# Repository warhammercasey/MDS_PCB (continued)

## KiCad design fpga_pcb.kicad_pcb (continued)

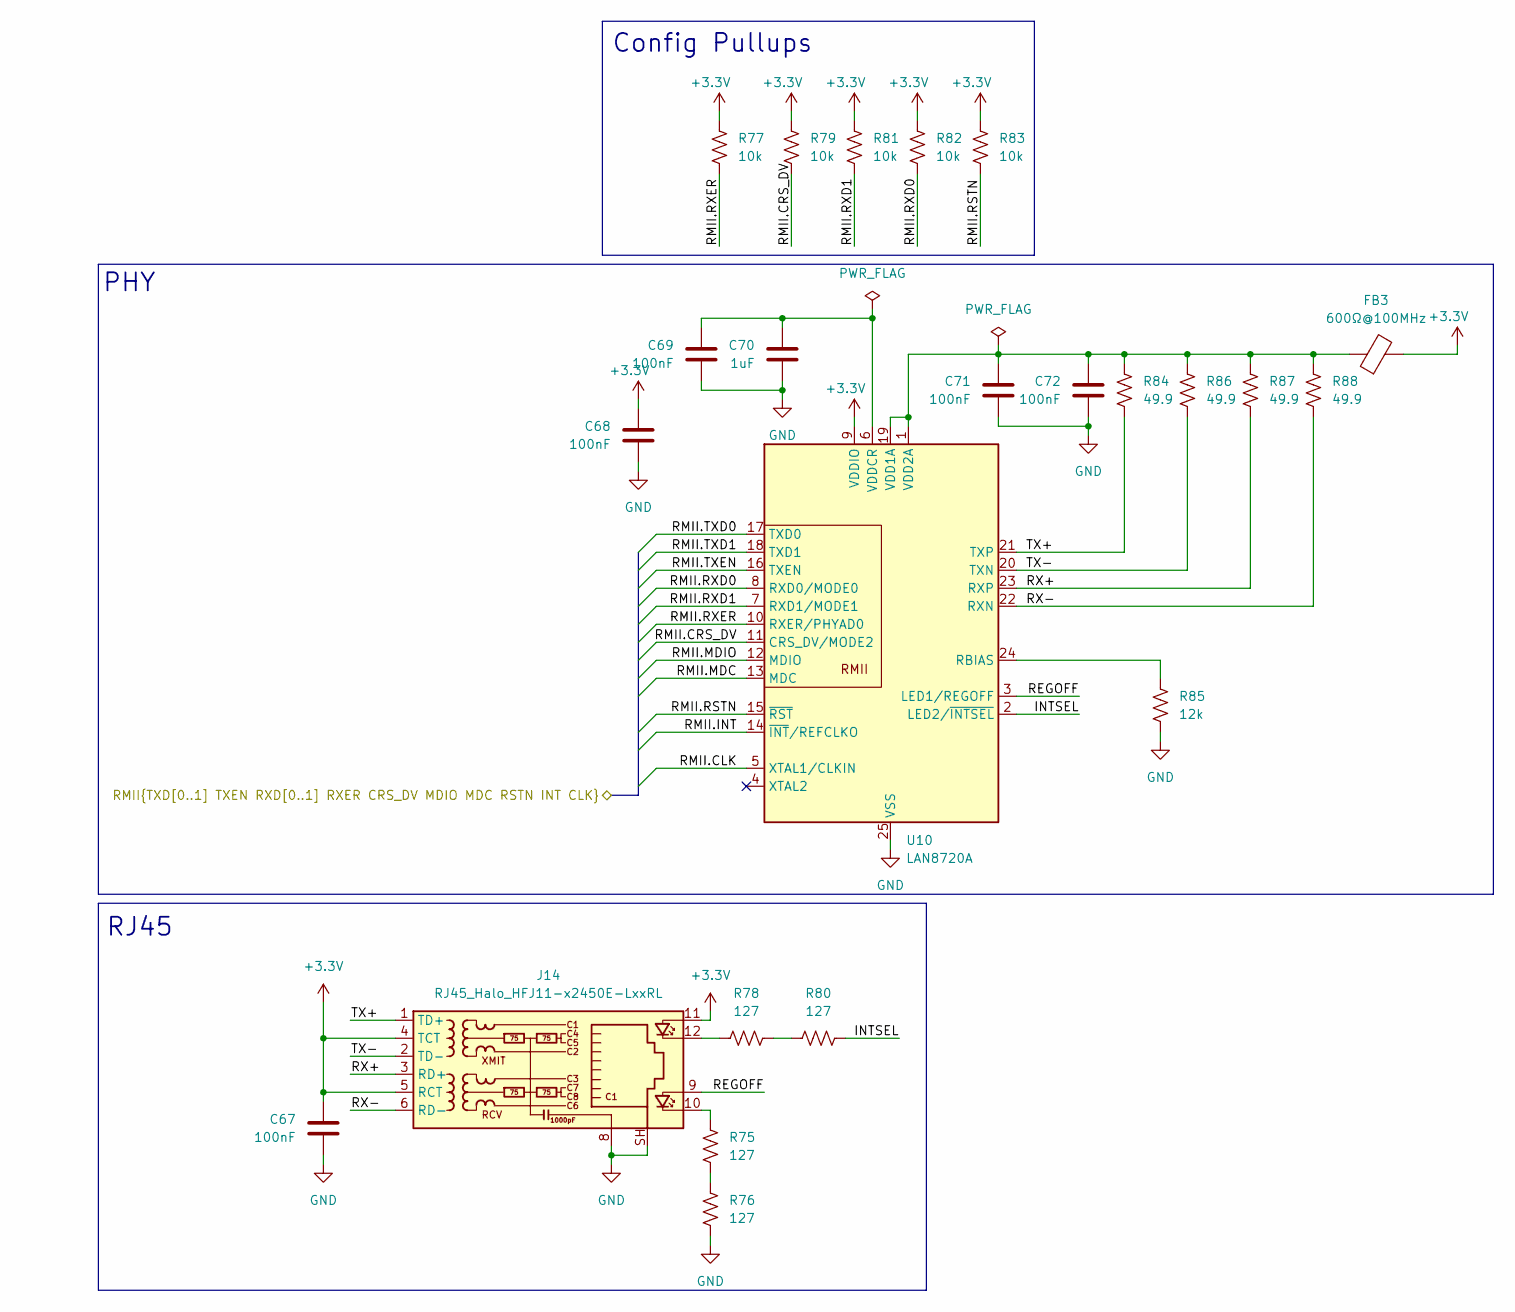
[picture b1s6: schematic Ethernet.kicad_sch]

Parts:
C67, C68, C69, C71, C72: 100nF; C_0603_1608Metric; Digikey PN 1276-6854-1-ND
C70: 1uF; C_0603_1608Metric; Digikey PN 1276-1859-1-ND
FB3: 600Ω@100MHz; L_0603_1608Metric; Digikey PN 490-1014-1-ND
J14: RJ45_Halo_HFJ11-x2450E-LxxRL; RJ45_HALO_HFJ11-x2450E-LxxRL_Horizontal; Digikey PN 5843-HFJ11-2450E-L12RL-ND
R75, R76, R78, R80: 127; R_0603_1608Metric; Digikey PN 311-127HRCT-ND
R77, R79, R81, R82, R83: 10k; R_0603_1608Metric; Digikey PN 311-10KLDCT-ND
R84, R86, R87, R88: 49.9; R_0603_1608Metric; Digikey PN 311-49.9HRCT-ND
R85: 12k; R_0603_1608Metric; Digikey PN 311-12.0KHRCT-ND
U10: LAN8720A; VQFN-24-1EP_4x4mm_P0.5mm_EP2.5x2.5mm_ThermalVias; Digikey PN LAN8720A-CP-CT-ND

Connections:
+3.3V: C67.1, C68.1, FB3.2, J14.4 (TCT), J14.5 (RCT), J14.11, R77.1, R79.1, R81.1, R82.1, R83.1, U10.9 (VDDIO); also elsewhere on the board
/Ethernet/INTSEL: R80.1, U10.2 (LED2/~INTSEL)
/Ethernet/REGOFF: J14.9, U10.3 (LED1/REGOFF)
/Ethernet/RMII.CLK: U10.5 (XTAL1/CLKIN); also elsewhere on the board
/Ethernet/RMII.CRS_DV: R79.2, U10.11 (CRS_DV/MODE2); also elsewhere on the board
/Ethernet/RMII.INT: U10.14 (~INT/REFCLKO); also elsewhere on the board
/Ethernet/RMII.MDC: U10.13 (MDC); also elsewhere on the board
/Ethernet/RMII.MDIO: U10.12 (MDIO); also elsewhere on the board
/Ethernet/RMII.RSTN: R83.2, U10.15 (~RST); also elsewhere on the board
/Ethernet/RMII.RXD0: R82.2, U10.8 (RXD0/MODE0); also elsewhere on the board
/Ethernet/RMII.RXD1: R81.2, U10.7 (RXD1/MODE1); also elsewhere on the board
/Ethernet/RMII.RXER: R77.2, U10.10 (RXER/PHYAD0); also elsewhere on the board
/Ethernet/RMII.TXD0: U10.17 (TXD0); also elsewhere on the board
/Ethernet/RMII.TXD1: U10.18 (TXD1); also elsewhere on the board
/Ethernet/RMII.TXEN: U10.16 (TXEN); also elsewhere on the board
/Ethernet/RX+: J14.3 (RD+), R87.2, U10.23 (RXP)
/Ethernet/RX-: J14.6 (RD-), R88.2, U10.22 (RXN)
/Ethernet/TX+: J14.1 (TD+), R84.2, U10.21 (TXP)
/Ethernet/TX-: J14.2 (TD-), R86.2, U10.20 (TXN)
GND: C67.2, C68.2, C69.2, C70.2, C71.2, C72.2, J14.8, J14.SH, R76.2, R85.2, U10.25 (VSS); also elsewhere on the board
unnamed: J14.10, R75.1
unnamed: J14.12, R78.2
unnamed: R75.2, R76.1
unnamed: R78.1, R80.2
unnamed: R85.1, U10.24 (RBIAS)
unnamed: C71.1, C72.1, FB3.1, R84.1, R86.1, R87.1, R88.1, U10.1 (VDD2A), U10.19 (VDD1A)
unnamed: C69.1, C70.1, U10.6 (VDDCR)

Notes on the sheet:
RJ45
Config Pullups
PHY

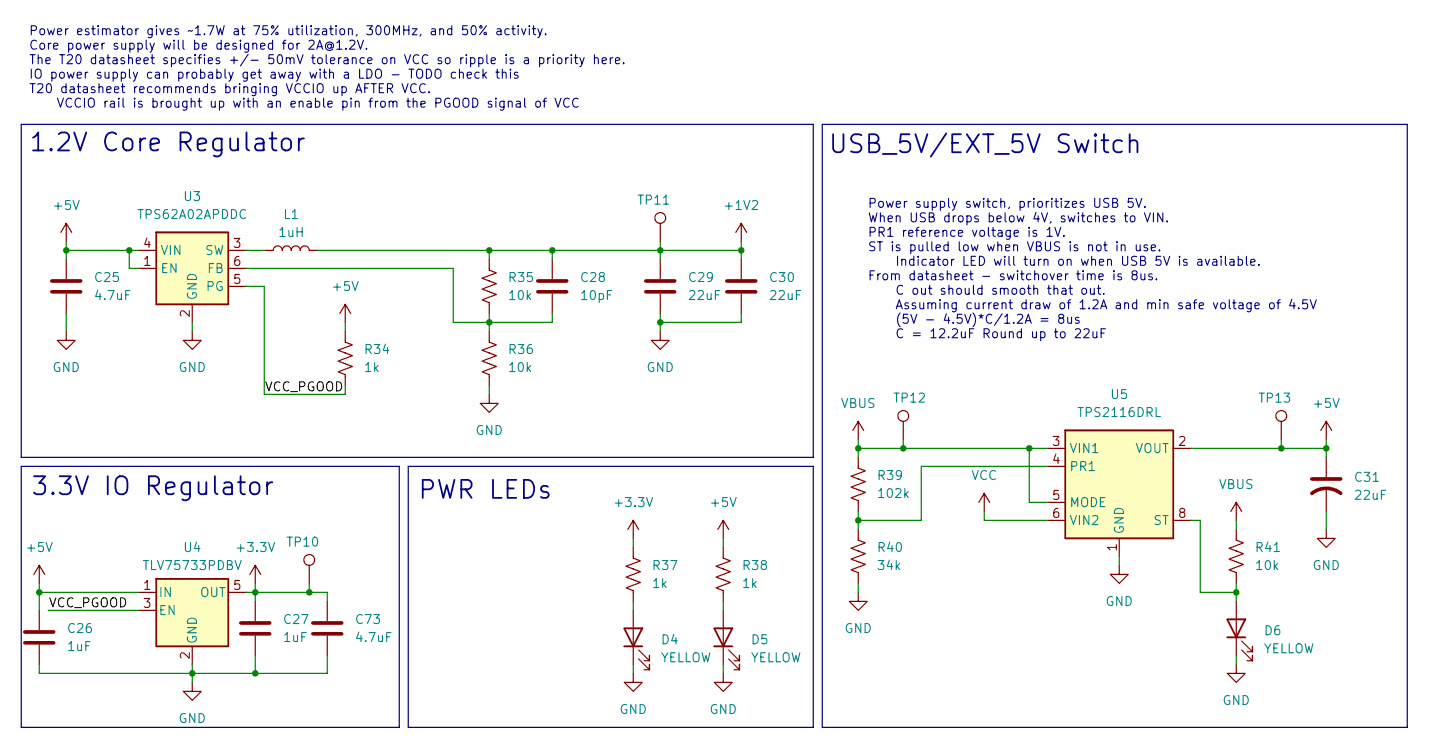
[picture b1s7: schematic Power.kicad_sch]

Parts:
C25, C73: 4.7uF; C_0603_1608Metric; Digikey PN 1276-1045-1-ND
C26, C27: 1uF; C_0603_1608Metric; Digikey PN 1276-1859-1-ND
C28: 10pF; C_0603_1608Metric; Digikey PN 1276-2149-1-ND
C29, C30: 22uF; C_1206_3216Metric; Digikey PN 1276-2728-1-ND
C31: 22uF; C_Radial_D5.0mm_H7.0mm_P2.00mm; Digikey PN P814-ND
D4, D5, D6: YELLOW; LED_0603_1608Metric; Digikey PN 754-1124-1-ND
L1: 1uH; L_1210_3225Metric; Digikey PN 3526-WIP322512A-1R0MLDGCT-ND
R34, R37, R38: 1k; R_0603_1608Metric; Digikey PN 311-1.00KHRCT-ND
R35, R36, R41: 10k; R_0603_1608Metric; Digikey PN 311-10KLDCT-ND
R39: 102k; R_0603_1608Metric; Digikey PN YAG1498CT-ND
R40: 34k; R_0603_1608Metric; Digikey PN 311-34.0KHRCT-ND
TP10, TP11, TP12, TP13: TestPoint; TestPoint_Pad_D1.0mm
U3: TPS62A02APDDC; SOT-23-6; Digikey PN 296-TPS62A02APDDCRCT-ND
U4: TLV75733PDBV; SOT-23-5; Digikey PN 296-TLV75733PDYDRCT-ND
U5: TPS2116DRL; SOT-583-8; Digikey PN 296-TPS2116DRLRCT-ND

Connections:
+1V2: C28.1, C29.1, C30.1, L1.2, R35.1, TP11.1 (1_1); also elsewhere on the board
+3.3V: C27.1, C73.1, R37.1, TP10.1 (1_1), U4.5 (OUT); also elsewhere on the board
+5V: C25.1, C26.1, C31.1, R34.1, R38.1, TP13.1 (1_1), U3.1 (EN), U3.4 (VIN), U4.1 (IN), U5.2 (VOUT), U5.7 (VOUT)
/Power/VCC_PGOOD: R34.2, U3.5 (PG), U4.3 (EN)
GND: C25.2, C26.2, C27.2, C29.2, C30.2, C31.2, C73.2, D4.1 (K), D5.1 (K), D6.1 (K), R36.2, R40.2, U3.2 (GND), U4.2 (GND), U5.1 (GND); also elsewhere on the board
unnamed: D4.2 (A), R37.2
unnamed: D5.2 (A), R38.2
unnamed: D6.2 (A), R41.2, U5.8 (ST)
unnamed: C28.2, R35.2, R36.1, U3.6 (FB)
unnamed: L1.1, U3.3 (SW)
unnamed: R39.2, R40.1, U5.4 (PR1)
VBUS: R39.1, R41.1, TP12.1 (1_1), U5.3 (VIN1), U5.5 (MODE); also elsewhere on the board
VCC: U5.6 (VIN2); also elsewhere on the board

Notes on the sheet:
USB_5V/EXT_5V Switch
PWR LEDs
Power estimator gives ~1.7W at 75% utilization, 300MHz, and 50% activity. Core power supply will be designed for 2A@1.2V. The T20 datasheet specifies +/- 50mV tolerance on VCC so ripple is a priority here. IO power supply can probably get away with a LDO - TODO check this T20 datasheet recommends b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
1.2V Core Regulator
Power supply switch, prioritizes USB 5V. When USB drops below 4V, switches to VIN. PR1 reference voltage is 1V. ST is pulled low when VBUS is not in use. Indicator LED will turn on when USB 5V is available. From datasheet - switchover time is 8us. C out should smooth that out. Assuming current draw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
3.3V IO Regulator

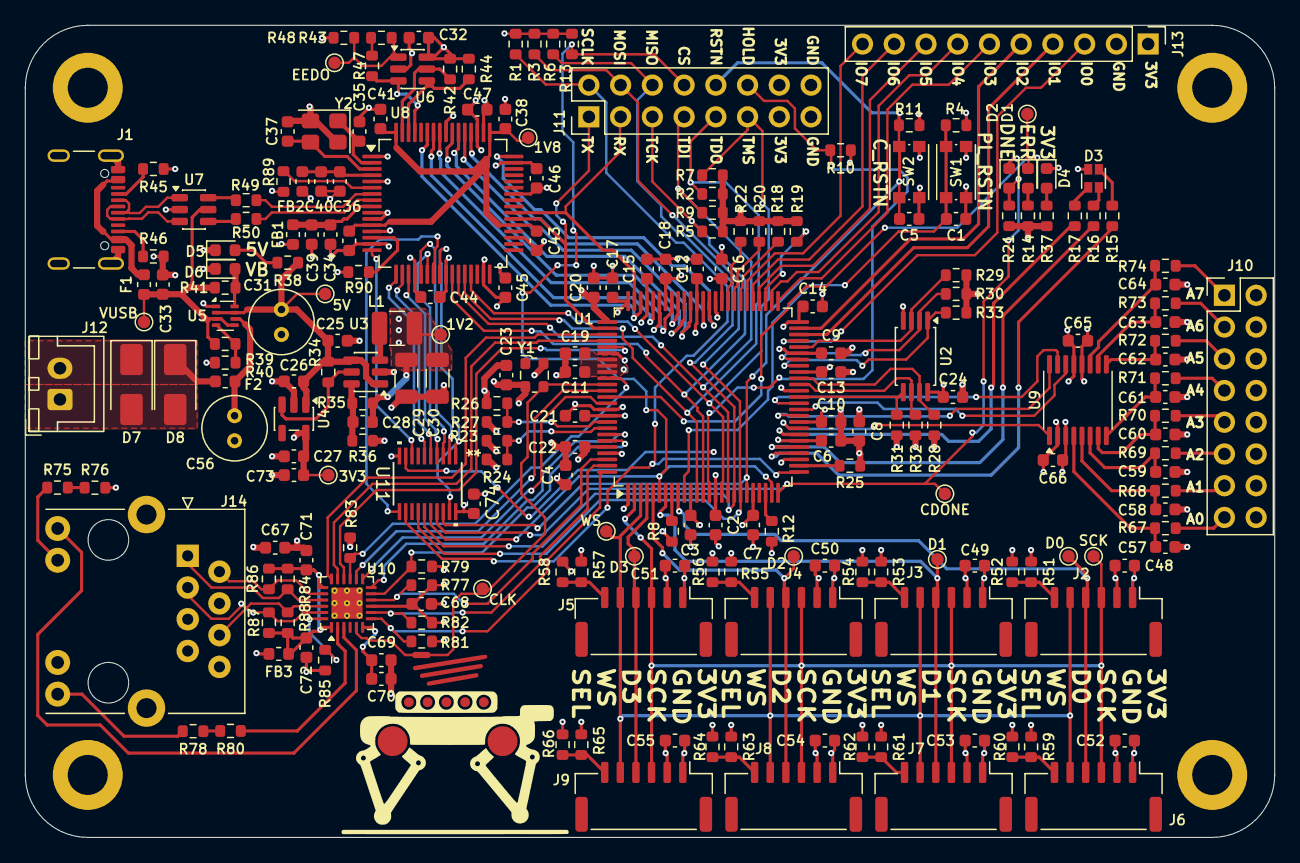
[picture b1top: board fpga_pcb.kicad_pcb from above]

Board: 4 copper layers, 100.0 x 65.0 mm, 227 parts (0 on the bottom side), 156 nets.

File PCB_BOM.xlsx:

Reference | Qty | Value | DNP | Exclude from BOM | Exclude from Board | Digikey PN | Unit Cost | Description | Total Cost | Board cost:
C1,C2,C3,C5,C6,C7,C9,C10,C12,C13,C15,C16,C17,C18,C19,C20,C21,C22,C23,C24,C32,C3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 | 46 | 100nF |  |  |  | 1276-6854-1-ND | 5.5E-2 | Unpolarized capacitor | 2.5299999999999998 | 56.957000000000001
C4,C8,C11,C14,C25,C34,C36,C38,C48,C49,C50,C51,C52,C53,C54,C55,C73 | 17 | 4.7uF |  |  |  | 1276-1045-1-ND | 4.3999999999999997E-2 | Unpolarized capacitor | 0.748
C26,C27,C33,C70 | 4 | 1uF |  |  |  | 1276-1859-1-ND | 0.1 | Unpolarized capacitor | 0.4
C28,C35,C37 | 3 | 10pF |  |  |  | 1276-2149-1-ND | 0.1 | Unpolarized capacitor | 0.30000000000000004
C29,C30 | 2 | 22uF |  |  |  | 1276-2728-1-ND | 0.28999999999999998 | Unpolarized capacitor | 0.57999999999999996
C31,C56 | 2 | 22uF |  |  |  | P814-ND | 0.27 | capacitor, US symbol | 0.54
D1 | 1 | RED |  |  |  | 754-1123-1-ND | 0.21 | Light emitting diode | 0.21
D2 | 1 | GREEN |  |  |  | 754-1121-1-ND | 0.19 | Light emitting diode | 0.19
D3 | 1 | LED_KRGB |  |  |  | 160-2162-1-ND | 0.44 | RGB LED, cathode/red/green/blue | 0.44
D4,D5,D6 | 3 | YELLOW |  |  |  | 754-1124-1-ND | 0.21 | Light emitting diode | 0.63
D7 | 1 | D |  |  |  | 5399-SS32CT-ND | 0.1 | Diode | 0.1
D8 | 1 | D_TVS |  |  |  | 5399-SMAJ6.0ACT-ND | 0.17 | Bidirectional transient-voltage-suppression diode | 0.17
F1,F2 | 2 | Fuse |  |  |  | 5923-0686F7000-01CT-ND | 0.45 | Fuse | 0.9
FB1,FB2,FB3 | 3 | 600Î©@100MHz |  |  |  | 490-1014-1-ND | 0.1 | Ferrite bead | 0.30000000000000004
J1 | 1 | USB_C_Receptacle_USB2.0_16P |  |  |  | 2073-USB4105-GF-ACT-ND | 0.8 | USB 2.0-only 16P Type-C Receptacle connector | 0.8
J2,J3,J4,J5,J6,J7,J8,J9 | 8 | Conn_01x06 |  |  |  | 455-BM06B-GHS-TBTCT-ND | 0.47 | Generic connector, single row, 01x06, script generated (kicad-library-utils/sch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 | 3.76
J10,J11 | 2 | Conn_02x08_Odd_Even |  |  |  | 4627-PH254V-216-6TBKG126-ND | 0.34 | Generic connector, double row, 02x08, odd/even pin numbering scheme (row 1 odd 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 | 0.68
J12 | 1 | 5VIN |  |  |  | 455-B2B-XH-A-ND | 0.1 | Generic connector, single row, 01x02, script generated (kicad-library-utils/sch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 | 0.1
J13 | 1 | Conn_01x10 |  |  |  | 2057-PH1-10-UA-ND | 0.14000000000000001 | Generic connector, single row, 01x10, script generated (kicad-library-utils/sch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 | 0.14000000000000001
J14 | 1 | RJ45_Halo_HFJ11-x2450E-LxxRL |  |  |  | 5843-HFJ11-2450E-L12RL-ND | 5.29 | Halo HFJ11, 10/100 Base-TX, two LEDs, RJ45, Shielded | 5.29
L1 | 1 | 1uH |  |  |  | 3526-WIP322512A-1R0MLDGCT-ND | 0.11 | Inductor | 0.11
R1,R2,R3,R4,R5,R6,R7,R8,R9,R10,R11,R12,R13,R18,R19,R20,R22,R24,R27,R35,R36,R41,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 | 38 | 10k |  |  |  | 311-10KLDCT-ND | 2.8000000000000001E-2 | Resistor, US symbol | 1.0640000000000001
R14,R15,R16,R17,R21,R28,R29,R30,R31,R32,R33,R34,R37,R38,R43,R47,R90 | 17 | 1k |  |  |  | 311-1.00KHRCT-ND | 2.5000000000000001E-2 | Resistor, US symbol | 0.42500000000000004
R25,R85,R89 | 3 | 12k |  |  |  | 311-12.0KHRCT-ND | 0.1 | Resistor, US symbol | 0.30000000000000004
R39 | 1 | 102k |  |  |  | YAG1498CT-ND | 0.11 | Resistor, US symbol | 0.11
R40 | 1 | 34k |  |  |  | 311-34.0KHRCT-ND | 0.11 | Resistor, US symbol | 0.11
R45,R46 | 2 | 5.1k |  |  |  | 311-5.1KGRCT-ND | 0.11 | Resistor, US symbol | 0.22
R49,R50 | 2 | 10 |  |  |  | 311-10LDCT-ND | 0.1 | Resistor, US symbol | 0.2
R67,R68,R69,R70,R71,R72,R73,R74,R75,R76,R78,R80 | 12 | 127 |  |  |  | 311-127HRCT-ND | 0.1 | Resistor, US symbol | 1.2000000000000002
R84,R86,R87,R88 | 4 | 49.9 |  |  |  | 311-49.9HRCT-ND | 0.11 | Resistor, US symbol | 0.44
SW1,SW2 | 2 | SW_Push |  |  |  | CKN10244CT-ND | 0.67 | Push button switch, generic, two pins | 1.34
U1 | 1 |  |  |  |  | 2134-T20Q100F3C3-ND | 10.3 |  | 10.3
U2 | 1 | 23AA02M-IST |  |  |  | 150-23AA02M-I/ST-ND | 3.18 | Microchip 2 Mbit SRAM Memory, up to 143MHz, 1.7-3.6V supply, TSSOP-8 | 3.18
U3 | 1 | TPS62A02APDDC |  |  |  | 296-TPS62A02APDDCRCT-ND | 0.24 | High Efficiency Synchronous Buck Converter with forced PWM, Adjustable Output 0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 | 0.24
U4 | 1 | TLV75733PDBV |  |  |  | 296-TLV75733PDYDRCT-ND | 0.37 | 1A Low IQ Small Size Low Dropout Voltage Regulator, Fixed Output 3.3V, SOT-23-5 | 0.37
U5 | 1 | TPS2116DRL |  |  |  | 296-TPS2116DRLRCT-ND | 1.07 | 2 Channnels Power Mux with Manual and Priority Switchover, 1.6-5.5V Input Volta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 | 1.07
U6 | 1 | 93AAxxBT-xOT |  |  |  | 93AA56BT-I/OTCT-ND | 0.32 | Serial EEPROM, 93 Series, 16-bit word, 1.8V, SOT-23 | 0.32
U7 | 1 | USBLC6-2SC6 |  |  |  | 497-5235-1-ND | 0.54 | Very low capacitance ESD protection diode, 2 data-line, SOT-23-6 | 0.54
U8 | 1 | FT4232H |  |  |  |  | 10 | Hi Speed Quad Channel USB UART/FIFO, LQFP/QFN-64 | 10
U9 | 1 | ADC1283 |  |  |  | ADC088S022CIMTX/NOPBCT-ND | 3.52 | Low power 8-channel single ended 12-bit SAR ADC, 50 ksps to 200 ksps, SPI, TSSO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 | 3.52
U10 | 1 | LAN8720A |  |  |  | LAN8720A-CP-CT-ND | 1.03 | LAN8720 Ethernet PHY with RMII interface, QFN-24 | 1.03
U11 | 1 | SN74LV244AQDGSRQ1 |  |  |  | 296-SN74LV244AQDGSRQ1CT-ND | 0.68 |  | 0.68
Y1 | 1 | ECS-2520MV-500-xx |  |  |  | XC2758CT-ND | 1.2 | HCMOS Crystal Clock Oscillator, 2.5x2.0 mm SMD | 1.2
Y2 | 1 | Crystal_GND24 |  |  |  | 2151-RH100-12.000-10-3030-TRCT-ND | 0.18 | Four pin crystal, GND on pins 2 and 4 | 0.18
